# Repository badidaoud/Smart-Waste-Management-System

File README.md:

# Smart Waste Management System

A LoRa-powered sensor that tells you how full a garbage bin actually is, so collection trucks stop guessing and start showing up for bins that actually need it. Four of us built this through Brilliant Catalyst Entrepreneurship, an optional program, not something we had to do for school, just something we wanted to build.

**Team:** Badi Daoud, Jay S., Kenneth Martinez, Mithuran
**My role:** hardware (PCB placement and routing) and the mechanical enclosure (SolidWorks)

> This is my own record of a project four of us built together. I'm documenting it honestly, including what didn't survive (no firmware source, no recovered presentation), and giving credit where it's due. Not a claim that I built it solo.

## Table of Contents

- [Overview](#overview)
- [Team and Roles](#team-and-roles)
- [System Architecture](#system-architecture)
- [Design Process](#design-process)
- [Hardware](#hardware)
- [Final Product](#final-product)
- [Mechanical and Enclosure Design](#mechanical-and-enclosure-design)
- [My Contributions](#my-contributions)
- [Repository Contents](#repository-contents)
- [Known Gaps](#known-gaps)

## Overview

Most waste collection runs on a fixed schedule instead of actual need, so trucks show up to bins that are half empty and skip ones that are already overflowing. We wanted to fix that with something cheap and low-power that just tells you how full a bin is, over a long-range wireless link, so nobody has to guess.

The idea: a battery-powered ESP32 sits on the bin, reads a capacity sensor, and reports back over LoRa to a receiving USB module plugged into a computer. No WiFi or cell signal needed out at the bin, which matters once you're covering a wide area with bins scattered all over the place.

## Team and Roles

Four of us built this through Brilliant Catalyst Entrepreneurship:

- **Jay S.** wrote the ESP32 firmware.
- **Kenneth Martinez** was the most experienced of the four of us. He reviewed everyone's work and ended up presenting the project.
- **Mithuran** pitched in on reviewing work when he could, though he was buried in university coursework for most of it.
- **Me (Badi)** handled the hardware: PCB placement and routing, plus the mechanical enclosure.

## System Architecture

*How power and signal move around the board: a 3.3V rail feeds the LoRa transmitter and the ESP32, a separate 5V rail runs through a TLV regulator into USB, and the ESP32 talks to the LoRa transmitter, which reports wirelessly to a receiving LoRa USB module plugged into a computer.*

## Design Process

Before any of this was a schematic, it was a napkin sketch:

*My first pass at it: USB-C charging a battery, running through a nano power timer and voltage regulator to power the ESP32, which drives the LoRa transmitter on one side and reads sensor input through I/O on the other.*

I'd never touched KiCad before this project. Learned it from scratch in under 20 days, just enough to turn that sketch into an actual board: placing components, wiring everything up, and figuring out the antenna keep-out zone the LoRa module needed.

## Hardware

The board runs on an ESP32-WROOM-32D talking to a LoRa transceiver (SX1278), with a BQ24072 handling battery charging, an FTDI chip for programming over USB, and a handful of switches and DIP pins for configuration. The full KiCad project is in [`hardware/kicad/`](hardware/kicad/), routed PCB layout included, not just pictures of it:

| File | Sheet | Contents |
|---|---|---|
| [`LoRa_schematic.kicad_sch`](hardware/kicad/LoRa_schematic.kicad_sch) | Root | ESP32-WROOM-32D, SX1278 LoRa transceiver, antenna, and configuration switches |
| [`untitled.kicad_sch`](hardware/kicad/untitled.kicad_sch) | USB in | USB-C input, MCP73831 Li-ion charger, TPS61200 boost converter, PMOS load switch |
| [`TLV.kicad_sch`](hardware/kicad/TLV.kicad_sch) | TLV (Regulator) | TLV75801 LDO regulator, FT231XQ USB-UART bridge for programming, status LED |
| [`power_block.kicad_sch`](hardware/kicad/power_block.kicad_sch) | Power block | BQ24072 battery management/charging, XC6220 3.3V regulator, thermistor |
| [`LoRa_schematic.kicad_pcb`](hardware/kicad/LoRa_schematic.kicad_pcb) | — | The routed PCB layout |
| [`LoRa_schematic.kicad_pro`](hardware/kicad/LoRa_schematic.kicad_pro) | — | KiCad project file tying the sheets together |

Here's what the layout actually looked like while I was working through it in the PCB editor:

<table>
<tr>
<td></td>
<td></td>
</tr>
<tr>
<td align="center"><em>First pass: components are down but nothing's routed yet, hence all the crisscrossing ratsnest lines</em></td>
<td align="center"><em>Second pass: regrouped everything to shorten the routing paths</em></td>
</tr>
</table>

*Zoomed in on the charging circuit (MCP73831), the boost converter (TPS61070), the battery footprint, and the keep-out zone the LoRa antenna needs, no copper or components allowed in that hatched area.*

## Final Product

<table>
<tr>
<td></td>
<td></td>
</tr>
<tr>
<td align="center"><em>Bare copper, nothing populated yet</em></td>
<td align="center"><em>Populated: battery holder, ESP32, LoRa module, buttons, status LED</em></td>
</tr>
<tr>
<td></td>
<td></td>
</tr>
<tr>
<td align="center"><em>Same board, different angle</em></td>
<td align="center"><em>And the isometric view, because it looks cool</em></td>
</tr>
</table>

## Mechanical and Enclosure Design

The sensor needed somewhere to actually live on the bin, so I modeled an enclosure in SolidWorks. Source files are in [`mechanical/`](mechanical/):

| File | Description |
|---|---|
| [`1_bin_lid.SLDPRT`](mechanical/1_bin_lid.SLDPRT) | Bin lid part |
| [`1_slot_bin.SLDPRT`](mechanical/1_slot_bin.SLDPRT) | Individual slot bin part |
| [`bins_combined_with_lids.SLDASM`](mechanical/bins_combined_with_lids.SLDASM) | Assembly combining multiple bins with their lids |
| [`outside_box.SLDPRT`](mechanical/outside_box.SLDPRT) | Outer enclosure box |

No renders survived for these, just the source files. Open them up in SolidWorks (or a compatible viewer) if you want to poke around.

## My Contributions

- Took our rough hand-sketched idea and actually built it out in KiCad, schematic and PCB layout, having never opened the program before this project.
- Placed and routed the whole board: the ESP32-WROOM-32D, the SX1278 LoRa transceiver, the BQ24072 battery management circuit, the TPS61070 boost regulator, the FTDI programming interface, and the antenna keep-out zone the LoRa module needs.
- Designed the physical enclosure in SolidWorks: the bin lid, the slot bin, the combined multi-bin assembly, and the outer box.

## Repository Contents

```
.
├── README.md
├── assets/                              Figures used in this README
├── hardware/
│   └── kicad/                            Full KiCad project: schematic sheets and routed PCB layout
└── mechanical/                          SolidWorks source files for the enclosure
    ├── 1_bin_lid.SLDPRT
    ├── 1_slot_bin.SLDPRT
    ├── bins_combined_with_lids.SLDASM
    └── outside_box.SLDPRT
```

## Known Gaps

Being straight about what's not here:

- Jay wrote and flashed the firmware straight from his own laptop when we met up, so there's no firmware source to include.
- The presentation got deleted by a teammate at some point, and nobody's found a copy since.

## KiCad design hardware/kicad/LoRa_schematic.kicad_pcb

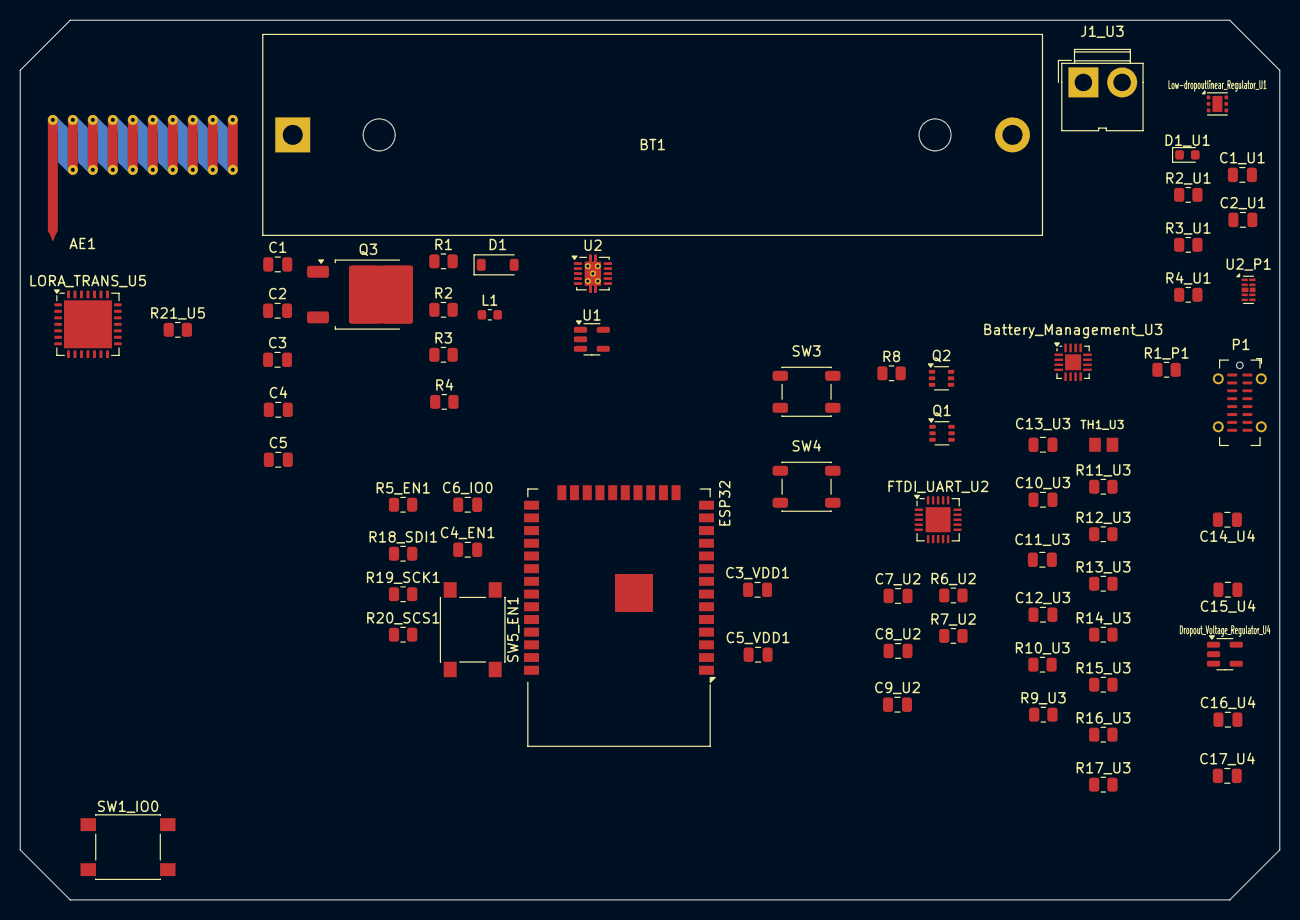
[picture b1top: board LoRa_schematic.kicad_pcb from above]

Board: 2 copper layers, 126.0 x 88.0 mm, 71 parts (0 on the bottom side), 54 nets, no tracks yet.

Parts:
AE1: Antenna; Texas_SWRA416_868MHz_915MHz
BT1: 3.7V; BatteryHolder_MPD_BH-18650-PC2
Battery_Management_U3: BQ24072RGT; VQFN-16-1EP_3x3mm_P0.5mm_EP1.6x1.6mm
C1, C2, C5, C15_U4: 4.7uF; C_0805_2012Metric
C1_U1, C2_U1, C5_VDD1, C11_U3, C12_U3, C13_U3, C17_U4: 10uF; C_0805_2012Metric
C3, C10_U3: 1uF; C_0805_2012Metric
C3_VDD1, C4_EN1, C6_IO0, C9_U2, C14_U4, C16_U4: 0.1uF; C_0805_2012Metric
C4: 22uF; C_0805_2012Metric
C7_U2, C8_U2: 47pF; C_0805_2012Metric
D1: D_Schottky; D_SOD-123
D1_U1: LED; LED_0603_1608Metric
Dropout_Voltage_Regulator_U4: XC6220B331MR; SOT-23-5
ESP32: ESP32-WROOM-32D
FTDI_UART_U2: FT231XQ; QFN-20-1EP_4x4mm_P0.5mm_EP2.5x2.5mm
J1_U3: Conn_01x02; JWT_A3963_1x02_P3.96mm_Vertical
L1: 2.2uH; L_0603_1608Metric
LORA_TRANS_U5: SX1278; QFN-28-1EP_6x6mm_P0.65mm_EP4.8x4.8mm
Low-dropoutlinear_Regulator_U1: TLV75801PDRV; WSON-6-1EP_2x2mm_P0.65mm_EP1x1.6mm
P1: USB_C_Plug_USB2.0; USB_C_Receptacle_G-Switch_GT-USB-7051x
Q1, Q2: MBT3904DW1; SOT-363_SC-70-6
Q3: Q_PMOS_DSG; TO-252-2
R1, R4, R5_EN1, R8, R14_U3, R15_U3: 10k; R_0805_2012Metric
R1_P1, R4_U1: 5.1k; R_0805_2012Metric
R2: 2M; R_0805_2012Metric
R2_U1: 1M; R_0805_2012Metric
R3: 180k; R_0805_2012Metric
R3_U1: 200k; R_0805_2012Metric
R6_U2, R7_U2: 27; R_0805_2012Metric
R9_U3, R10_U3, R12_U3: 100k; R_0805_2012Metric
R11_U3: 1.5k; R_0805_2012Metric
R13_U3: 71.5k; R_0805_2012Metric
R16_U3: 2.2k; R_0805_2012Metric
R17_U3: 4.99k; R_0805_2012Metric
R18_SDI1, R19_SCK1, R20_SCS1, R21_U5: 22; R_0805_2012Metric
SW1_IO0: BOOT; SW_SPST_PTS645
SW3, SW4: SW_DIP_x01; SW_SPST_PTS647_Sx50
SW5_EN1: RESET; SW_SPST_PTS645
TH1_U3: 10K; THRMC2012X130N
U1: MCP73831-2-OT; SOT-23-5
U2: TPS61200DRC; Texas_S-PVSON-N10_ThermalVias
U2_P1: D3V3XA4B10LP; Diodes_UDFN-10_1.0x2.5mm_P0.5mm

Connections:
3V3: C14_U4.1, C15_U4.1, Dropout_Voltage_Regulator_U4.5 (VOUT), R9_U3.2, R10_U3.2
/100: C6_IO0.1, ESP32.25 (IO0), SW1_IO0.2
/CLK_I: LORA_TRANS_U5.16 (SCK), R19_SCK1.1
/CS_I: LORA_TRANS_U5.19 (NSS), R20_SCS1.1
/DATA_I: LORA_TRANS_U5.18 (MOSI), R18_SDI1.1
/DATA_O: ESP32.21 (SDO/SD0), R21_U5.1
/DTR: Q2.6 (C1), R8.1
/EN: Q1.6 (C1), SW4.1
/Power block/5V: Battery_Management_U3.13 (IN), C10_U3.2, C11_U3.2, R15_U3.1
/Power block/CHG: Battery_Management_U3.9 (~CHG), R10_U3.1
/Power block/CHG_OUT: C16_U4.1, C17_U4.1, Dropout_Voltage_Regulator_U4.1 (VIN), Dropout_Voltage_Regulator_U4.3 (CE)
/Power block/PGOOD: Battery_Management_U3.7 (~PGOOD), R9_U3.1
/RTS: Q1.1 (E1), Q2.2 (B1)
/TLV/5V: C1_U1.1, Low-dropoutlinear_Regulator_U1.4 (EN), Low-dropoutlinear_Regulator_U1.6 (IN)
/TLV/USB_DM: C8_U2.1, R6_U2.1
/TLV/USB_DP: C7_U2.1, R7_U2.1
/USB in/5V: C4.1, D1.1 (K), U2.2 (VOUT), U2.10 (FB), U2_P1.4, U2_P1.7 (NC)
/USB in/USB_N: P1.A7 (D-), U2_P1.1, U2_P1.10 (NC)
/USB in/USB_P: P1.A6 (D+), U2_P1.2, U2_P1.9 (NC)
GND: BT1.2 (-), Battery_Management_U3.8 (VSS), Battery_Management_U3.17 (VSS), C1.2, C1_U1.2, C2.2, C2_U1.2, C3.2, C3_VDD1.2, C4.2, C4_EN1.2, C5.2, C5_VDD1.2, C6_IO0.2, C7_U2.2, C8_U2.2, C9_U2.2, C10_U3.1, C11_U3.1, C12_U3.1, C13_U3.2, C14_U4.2, C15_U4.2, C16_U4.2, C17_U4.2, D1_U1.1 (K), Dropout_Voltage_Regulator_U4.2 (GND), ESP32.1 (GND), ESP32.15 (GND), ESP32.38 (GND), ESP32.39 (GND), FTDI_UART_U2.3 (GND), FTDI_UART_U2.13 (GND), FTDI_UART_U2.21 (GND), J1_U3.1, LORA_TRANS_U5.15 (GND), LORA_TRANS_U5.21 (GND), LORA_TRANS_U5.22 (GND), LORA_TRANS_U5.23 (GND), LORA_TRANS_U5.26 (GND), LORA_TRANS_U5.29 (GND), Low-dropoutlinear_Regulator_U1.3 (GND), Low-dropoutlinear_Regulator_U1.7 (GND), P1.A1 (GND), P1.A12 (GND), P1.B1 (GND), P1.B12 (GND), P1.S1 (SHIELD), R1.2, R1_P1.2, R3.2, R3_U1.2, R4.2, R11_U3.1, R12_U3.1, R13_U3.1, R14_U3.1, R16_U3.1, R17_U3.1, SW1_IO0.1, SW3.2, SW4.2, SW5_EN1.1, TH1_U3.2, U1.2 (V_{SS}), U2.4 (PGND), U2.9 (GND), U2.11 (PAD), U2_P1.3 (VSS), U2_P1.8 (VSS)
unnamed: AE1.1 (A), LORA_TRANS_U5.28 (RFO_LF)
unnamed: BT1.1 (+), C1.1, Q3.2 (S), U1.3 (V_{BAT})
unnamed: Battery_Management_U3.6 (EN1), R14_U3.2
unnamed: Battery_Management_U3.5 (EN2), R15_U3.2
unnamed: Battery_Management_U3.12 (ILIM), R16_U3.2
unnamed: Battery_Management_U3.16 (ISET), R17_U3.2
unnamed: Battery_Management_U3.10 (OUT), Battery_Management_U3.11 (OUT), C12_U3.2
unnamed: Battery_Management_U3.15 (TD), R11_U3.2
unnamed: Battery_Management_U3.14 (TMR), R13_U3.2
unnamed: Battery_Management_U3.1 (TS), TH1_U3.1
unnamed: Battery_Management_U3.4 (~CE), R12_U3.2
unnamed: C2.1, D1.2 (A), P1.A4 (VBUS), P1.A9 (VBUS), P1.B4 (VBUS), P1.B9 (VBUS), Q3.3 (G), R4.1, U1.4 (V_{DD})
unnamed: D1_U1.2 (A), R4_U1.2
unnamed: C4_EN1.1, ESP32.3 (EN), LORA_TRANS_U5.7 (~RESET), R5_EN1.2, SW5_EN1.2
unnamed: ESP32.26 (IO4), LORA_TRANS_U5.12 (DIO4)
unnamed: ESP32.20 (SCK/CLK), R19_SCK1.2
unnamed: ESP32.19 (SCS/CMD), R20_SCS1.2
unnamed: ESP32.22 (SDI/SD1), R18_SDI1.2
unnamed: C3_VDD1.1, C5_VDD1.1, ESP32.2 (VDD)
unnamed: C9_U2.1, FTDI_UART_U2.10 (3V3OUT), FTDI_UART_U2.11 (~RESET), FTDI_UART_U2.20 (VCCIO)
unnamed: FTDI_UART_U2.9 (USBDM), R6_U2.2
unnamed: FTDI_UART_U2.8 (USBDP), R7_U2.2
unnamed: Battery_Management_U3.2 (BAT), Battery_Management_U3.3 (BAT), C13_U3.1, J1_U3.2
unnamed: LORA_TRANS_U5.17 (MISO), R21_U5.2
unnamed: Low-dropoutlinear_Regulator_U1.2 (FB), R2_U1.2, R3_U1.1
unnamed: C2_U1.1, Low-dropoutlinear_Regulator_U1.1 (OUT), R2_U1.1, R4_U1.1
unnamed: P1.A5 (CC), R1_P1.1
unnamed: Q1.2 (B1), R8.2
unnamed: Q2.1 (E1), SW3.1
unnamed: C5.1, L1.1, Q3.1 (D), R2.1, U2.5 (VIN), U2.6 (EN), U2.8 (PS)
unnamed: R1.1, U1.5 (PROG)
unnamed: L1.2, U2.3 (L)
unnamed: R2.2, R3.1, U2.7 (UVLO)
unnamed: C3.1, U2.1 (VAUX)
